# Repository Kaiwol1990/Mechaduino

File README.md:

Derivation of the original Mechaduino code from jcchurch13.

# Firmware
### Changes:

- added an enable pin (pin 2, only 3.3 V compatible)
- Menu entry for generating a step response
- Menu entry for generating a dirac delta function
- deleted all modes other than position 
- changed all float to integer operations
- added some filtering to the effort and D-Term
- Changed the frequency of the PID loop to 5 kHz
- Encoder readings are placed in its own ISR that runs with 10 kHz (oversampling)
- maximal step frequency = 40 kHz
- changed the PWM resolution from 8 bit to 9 bit
- PID auto tuning
- The lookup table is now in its own file (lookup_table.cpp)
- The Parameters are now in Configuration.cpp
- Added Language file for easy translation
- added an invert direction setting
- simple error register to save if an error occurred
- LED shows errors by different blinking patterns
- downhill simplex algorithm to fine tune the pid settings

### LED blink pattern:
If an error occures the led will switch from constant on to different patterns. These patterns are separated from each other by a longer pause. After this pause one pattern will be shown and then after the pause the next pattern will be shown.

|Pattern| Error|
|-------|------|
|Fast blinking | Timing error. This can occur if the mechaduino receives too much steps. Consider lowering your microsteps or limit the maximal speed|
|Long on | maximal error was reached|
|Long on, one flash | the maximal current was reached|
|Long on, two flashs | the lookup table shows some errors|

### List of commands
To get an list of the possible commands send help over the serial monitor

|Command|Description|Arguments|
|-------|-----------|---------|
|help | prints this menu |
|calibrate | starts the calibration routine | -check -smooth |
|diagnose | read Encoder Diagnostics | |
|state | shows and sets the motor state | -on, -off |
|stream | streams servo parameters | -f {int}, -on, -off |
|parameter | Get or set parameter | -set {-parameter} {value}, -get |
|error | get or reset the error register | -reset |
|dirac | generates a Delta-Distribution | -f {int} |
|response | generates a step response | -f {int}, -s {int} |
|error | get or reset the error register | -reset |
|autotune | PID auto tune | -c {byte}, -d |
|downhill | Downhhill simplex algorithm | -f {int}, -v {int}, -o |
|testmove | Starts a testmove for the servo | -f {int}, -v {int}, -o |
|interrupt | Starts or stops the ISR | -TC5 {bool}, -TC4 {bool} |

# Windows GUI

- Live view/stream motor parameter (angle, error, effort, ...)
- generate and analyze different test moves with different sampling rates (step response, dirac delta function, ...)
- change parameters without the need of serial commands
- generate a configuration file 
- Log streamed motor parameter as txt or csv file

# License
All Mechaduino related materials are released under the Creative Commons Attribution Share-Alike 4.0 License
https://creativecommons.org/licenses/by-sa/4.0/

Much of the work is based on Mechaduino project:
https://github.com/jcchurch13/Mechaduino-Firmware

# Support
If you want to support me for further improvements and things like that, you can send me a small kickback with PayPal

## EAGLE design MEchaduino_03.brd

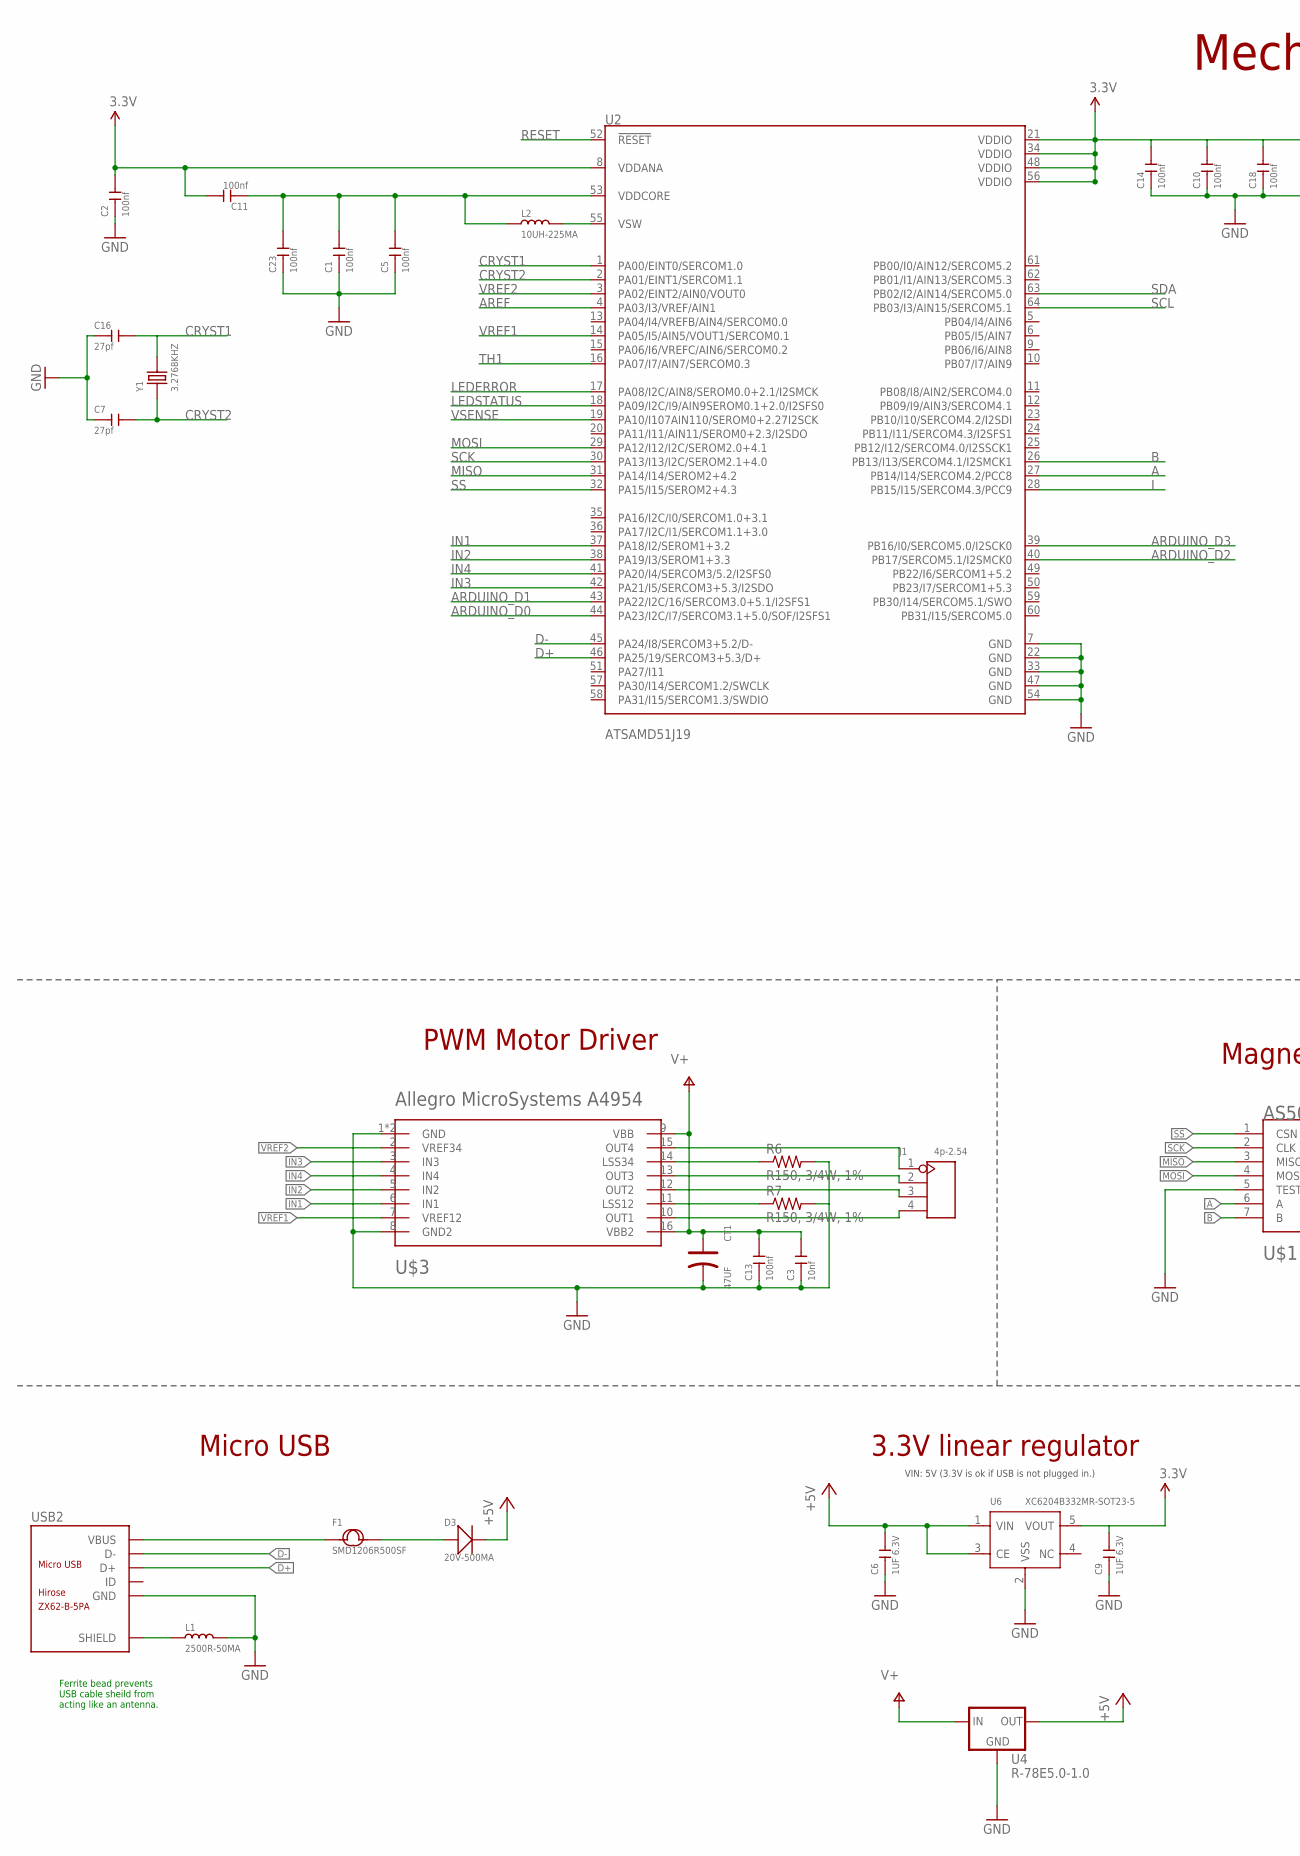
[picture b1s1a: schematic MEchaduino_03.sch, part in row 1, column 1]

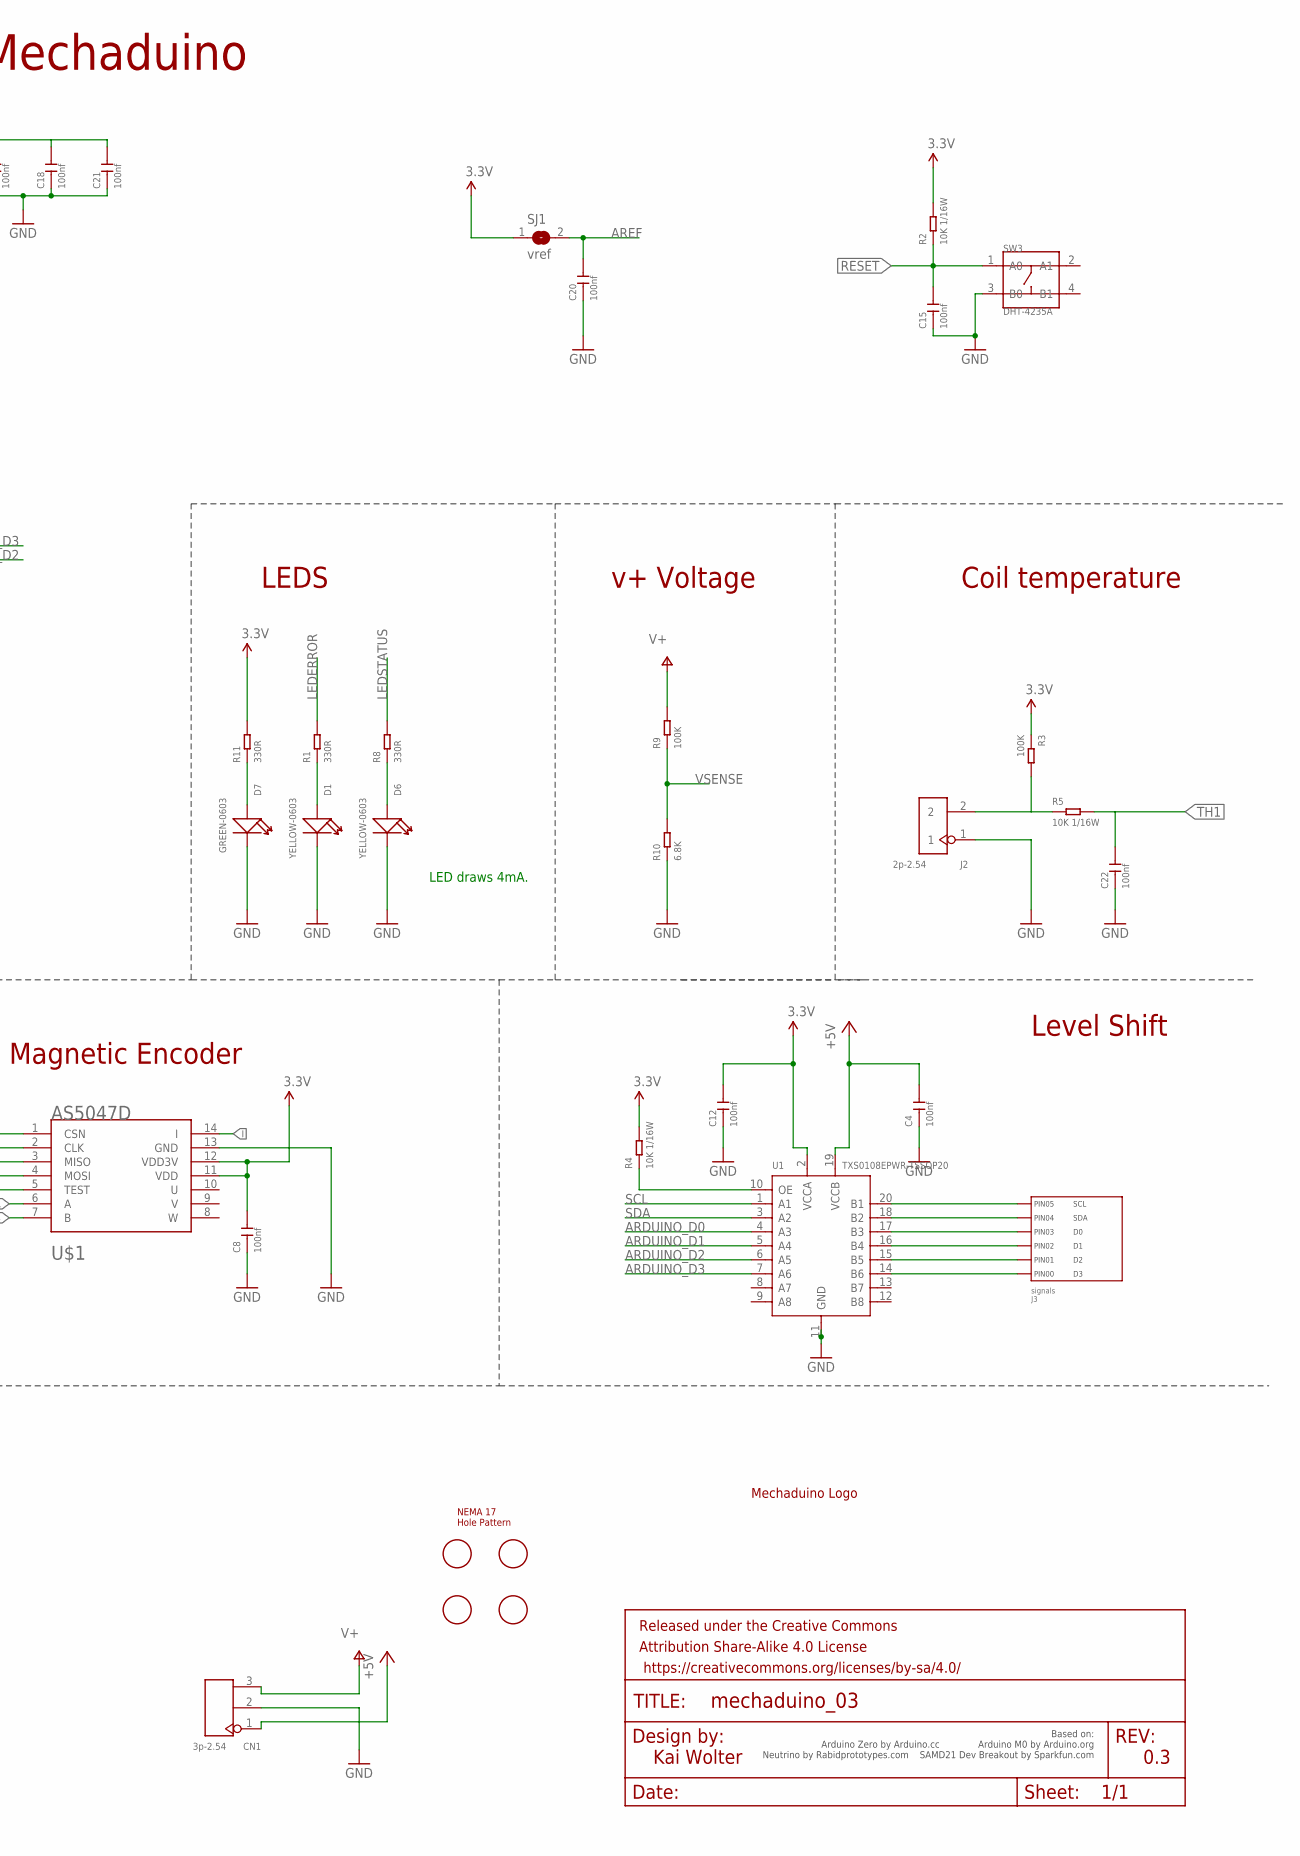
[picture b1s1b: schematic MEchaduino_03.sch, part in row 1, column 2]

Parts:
C1, C2, C4, C5, C8, C10, C11, C12, C14, C15, C18, C20, C21, C22, C23: 100nf; C0402
C3: 10nf; C0603
C6, C9: 1UF 6.3V; C0402
C7, C16: 27pf; C0402
C13: 100nf; C0603
CN1: 3p-2.54; H3-2.54
CT1: 47UF; ELECTRO-SMD-C-6MM
D1, D6: YELLOW-0603; LED-0603
D3: 20V-500MA; SOD-123
D7: GREEN-0603; LED-0603
F1: SMD1206R500SF; F1206
FRAME1: FRAME-LEDGER; CREATIVE_COMMONS
J1: 4p-2.54; H4-2.54
J2: 2p-2.54; H2-2.54
J3: signals; PTH_2.54MM_01X06
L1: 2500R-50MA; L0603
L2: 10UH-225MA; L0806
R1, R8, R11: 330R; R0402
R2, R4, R5: 10K 1/16W; R0402
R3, R9: 100K; R0402
R6, R7: R150, 3/4W, 1%; R1206; MPN KRL1632E-M-R150-F-T5
R10: 6.8K; R0603
SJ1: vref; SJ
SW3: DHT-4235A; SW4-SMD-4.2X3.2X2.5MM
U1: TXS0108EPWR-TSSOP20; TSSOP20-0.65-6.5X4.4MM
U2: ATSAMD51J19; TQFP64; MPN ATSAMD51J19A-AU
U4: R-78E5.0-1.0; DC-DC_CONVERTER_78XX
U6: XC6204B332MR-SOT23-5; SOT-23-5
U$1: AS5047D; TSSOP14; MPN AS5047D-ATSM
U$2: NEMA17_HOLE_PATTERNNEW; NEMA17_HOLE_PATTERN_2
U$3: Allegro MicroSystems A4954; TSSOP16_THERM; MPN A4953ELJTR-T
U$4: MECHADUINO_LOGO
USB2: ZX62-B-5PA; MICRO-USB5+6P-SMD-0.65-AB
Y1: 3.2768KHZ; X2-SMD-L2.0X1.2X0.55MM

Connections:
3.3V: C2.2, C8.2, C9.2, C10.2, C11.2, C12.2, C14.2, C18.2, C21.2, R2.2, R3.1, R4.2, R11.2, SJ1.1, U1.2 (VCCA), U2.8 (VDDANA), U2.21 (VDDIO), U2.34 (VDDIO), U2.48 (VDDIO), U2.56 (VDDIO), U6.5 (VOUT), U$1.11 (VDD), U$1.12 (VDD3V)
+5V: C4.2, C6.2, CN1.1, D3.-, U1.19 (VCCB), U4.VOUT (OUT), U6.1 (VIN), U6.3 (CE)
A: U2.27 (PB14/I14/SERCOM4.2/PCC8), U$1.6 (A)
ARDUINO_D0: U1.4 (A3), U2.44 (PA23/I2C/I7/SERCOM3.1+5.0/SOF/I2SFS1)
ARDUINO_D1: U1.5 (A4), U2.43 (PA22/I2C/16/SERCOM3.0+5.1/I2SFS1)
ARDUINO_D2: U1.6 (A5), U2.40 (PB17/SERCOM5.1/I2SMCK0)
ARDUINO_D3: U1.7 (A6), U2.39 (PB16/I0/SERCOM5.0/I2SCK0)
AREF: C20.2, SJ1.2, U2.4 (PA03/I3/VREF/AIN1)
B: U2.26 (PB13/I13/SERCOM4.1/I2SMCK1), U$1.7 (B)
CRYST1: C16.2, U2.1 (PA00/EINT0/SERCOM1.0), Y1.2
CRYST2: C7.2, U2.2 (PA01/EINT1/SERCOM1.1), Y1.1
D+: U2.46 (PA25/19/SERCOM3+5.3/D+), USB2.3 (D+)
D-: U2.45 (PA24/I8/SERCOM3+5.2/D-), USB2.2 (D-)
GND: C1.1, C2.1, C3.1, C4.1, C5.1, C6.1, C7.1, C8.1, C9.1, C10.1, C12.1, C13.1, C14.1, C15.1, C16.1, C18.1, C20.1, C21.1, C22.1, C23.1, CN1.2, CT1.-, D1.-, D6.-, D7.-, J2.1, L1.2, R6.2, R7.2, R10.1, SW3.3 (B0), U1.11 (GND), U2.7 (GND), U2.22 (GND), U2.33 (GND), U2.47 (GND), U2.54 (GND), U4.GND, U6.2 (VSS), U$1.5 (TEST), U$1.13 (GND), U$3.1 (GND), U$3.8 (GND2), U$3.P$1 (GND), USB2.5 (GND)
I: U2.28 (PB15/I15/SERCOM4.3/PCC9), U$1.14 (I)
IN1: U2.37 (PA18/I2/SEROM1+3.2), U$3.6 (IN1)
IN2: U2.38 (PA19/I3/SEROM1+3.3), U$3.5 (IN2)
IN3: U2.42 (PA21/I5/SERCOM3+5.3/I2SDO), U$3.3 (IN3)
IN4: U2.41 (PA20/I4/SERCOM3/5.2/I2SFS0), U$3.4 (IN4)
I_SENSE_COIL_A: R7.1, U$3.11 (LSS12)
I_SENSE_COIL_B: R6.1, U$3.14 (LSS34)
LEDERROR: R1.2, U2.17 (PA08/I2C/AIN8/SEROM0.0+2.1/I2SMCK)
LEDSTATUS: R8.2, U2.18 (PA09/I2C/I9/AIN9SEROM0.1+2.0/I2SFS0)
MISO: U2.31 (PA14/I14/SEROM2+4.2), U$1.3 (MISO)
MOSI: U2.29 (PA12/I12/I2C/SEROM2.0+4.1), U$1.4 (MOSI)
unnamed: D6.+, R8.1
unnamed: J3.P$4 (PIN3), U1.17 (B3)
unnamed: D1.+, R1.1
unnamed: J3.P$3 (PIN2), U1.16 (B4)
unnamed: J3.P$2 (PIN1), U1.15 (B5)
unnamed: R4.1, U1.10 (OE)
unnamed: J3.P$1 (PIN0), U1.14 (B6)
unnamed: C1.2, C5.2, C11.1, C23.2, L2.1, U2.53 (VDDCORE)
unnamed: J3.P$6 (PIN5), U1.20 (B1)
unnamed: L2.2, U2.55 (VSW)
unnamed: D7.+, R11.1
unnamed: D3.+, F1.2
unnamed: J1.1, U$3.15 (OUT4)
unnamed: J1.4, U$3.10 (OUT1)
unnamed: J1.3, U$3.12 (OUT2)
unnamed: J1.2, U$3.13 (OUT3)
unnamed: J3.P$5 (PIN4), U1.18 (B2)
unnamed: J2.2, R3.2, R5.1
RESET: C15.2, R2.1, SW3.1 (A0), U2.52 (!RESET!)
SCK: U2.30 (PA13/I13/I2C/SEROM2.1+4.0), U$1.2 (CLK)
SCL: U1.1 (A1), U2.64 (PB03/I3/AIN15/SERCOM5.1)
SDA: U1.3 (A2), U2.63 (PB02/I2/AIN14/SERCOM5.0)
SHIELD: L1.1, USB2.P1 (SHIELD), USB2.P2 (SHIELD), USB2.P3 (SHIELD), USB2.P4 (SHIELD), USB2.P5 (SHIELD), USB2.P6 (SHIELD)
SS: U2.32 (PA15/I15/SEROM2+4.3), U$1.1 (CSN)
TH1: C22.2, R5.2, U2.16 (PA07/I7/AIN7/SERCOM0.3)
V+: C3.2, C13.2, CN1.3, CT1.+, R9.2, U4.VIN (IN), U$3.9 (VBB), U$3.16 (VBB2)
VBUS: F1.1, USB2.1 (VBUS)
VREF1: U2.14 (PA05/I5/AIN5/VOUT1/SERCOM0.1), U$3.7 (VREF12)
VREF2: U2.3 (PA02/EINT2/AIN0/VOUT0), U$3.2 (VREF34)
VSENSE: R9.1, R10.2, U2.19 (PA10/I107AIN110/SEROM0+2.27I2SCK)

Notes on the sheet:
LED draws 4mA.
Ferrite bead prevents USB cable sheild from acting like an antenna.
3.3V linear regulator
Magnetic Encoder
PWM Motor Driver
VIN: 5V (3.3V is ok if USB is not plugged in.)
Micro USB
Kai Wolter
Based on: Arduino Zero by Arduino.cc Arduino M0 by Arduino.org Neutrino by Rabidprototypes.com SAMD21 Dev Breakout by Sparkfun.com
0.3
Mechaduino
Level Shift
Coil temperature
v+ Voltage
LEDS

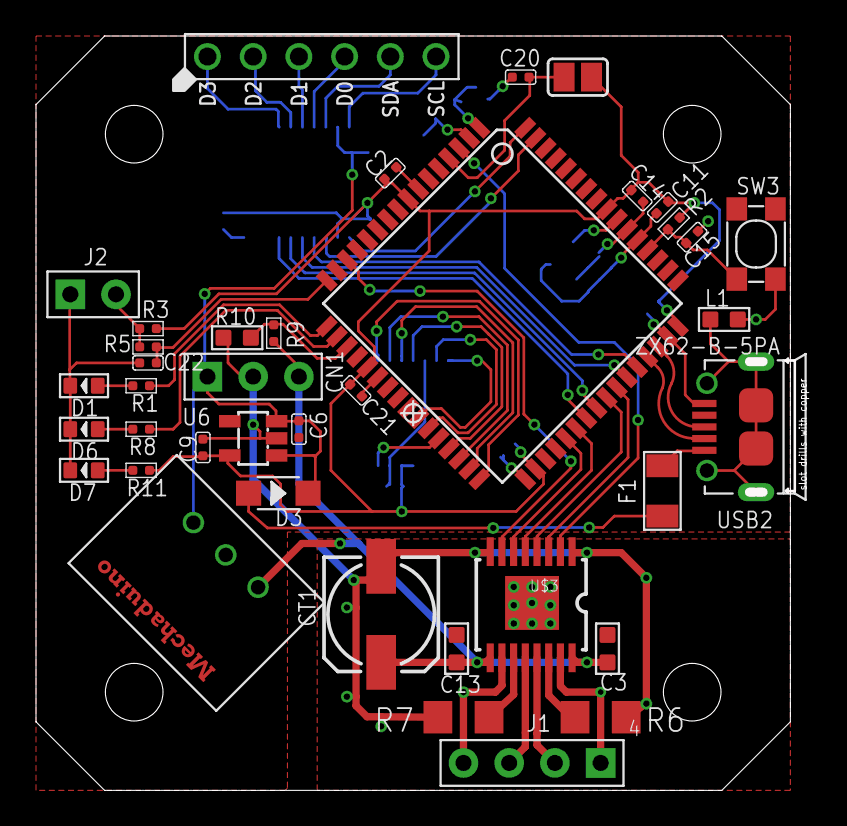
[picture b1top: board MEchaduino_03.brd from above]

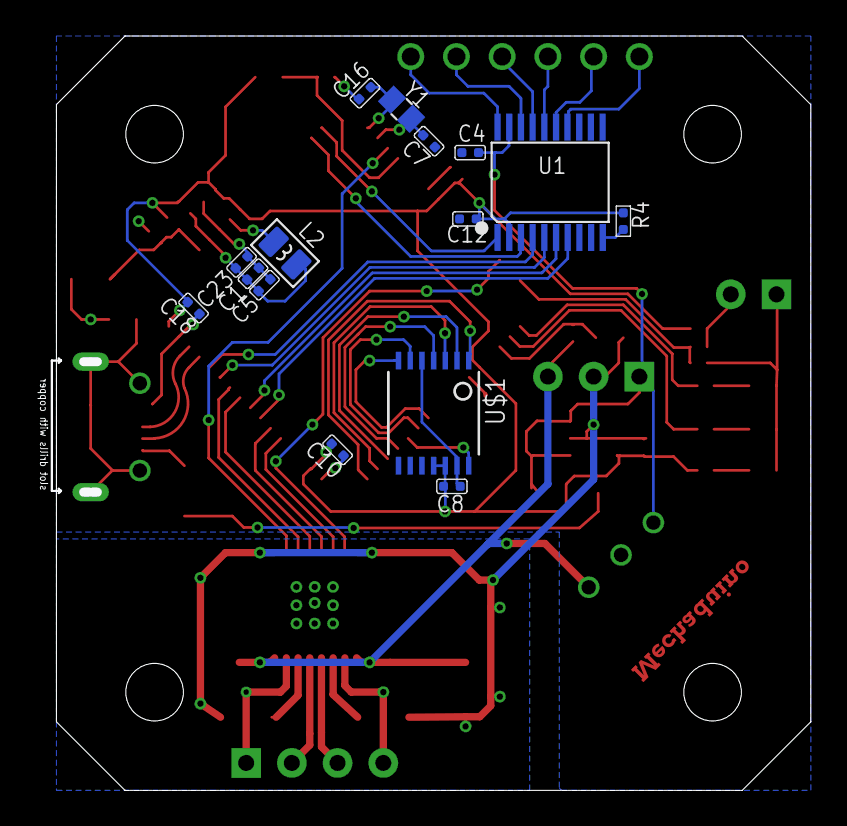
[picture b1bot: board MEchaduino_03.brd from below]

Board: 2 copper layers, 41.9 x 41.9 mm, 57 parts (15 on the bottom side), 55 nets.

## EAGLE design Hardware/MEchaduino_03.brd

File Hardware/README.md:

Derivation of the original Mechaduino code from jcchurch13.

# Firmware
### Changes:

- added an enable pin (pin 2, only 3.3 V compatible)
- Menu entry for generating a step response
- Menu entry for generating a dirac delta function
- deleted all modes other than position 
- changed all float to integer operations
- added some filtering to the effort and D-Term
- Changed the frequency of the PID loop to 5 kHz
- Encoder readings are placed in its own ISR that runs with 10 kHz (oversampling)
- maximal step frequency = 40 kHz
- changed the PWM resolution from 8 bit to 9 bit
- PID auto tuning
- The lookup table is now in its own file (lookup_table.cpp)
- The Parameters are now in Configuration.cpp
- Added Language file for easy translation
- added an invert direction setting
- simple error register to save if an error occurred
- LED shows errors by different blinking patterns
- downhill simplex algorithm to fine tune the pid settings

### LED blink pattern:
If an error occures the led will switch from constant on to different patterns. These patterns are separated from each other by a longer pause. After this pause one pattern will be shown and then after the pause the next pattern will be shown.

|Pattern| Error|
|-------|------|
|Fast blinking | Timing error. This can occur if the mechaduino receives too much steps. Consider lowering your microsteps or limit the maximal speed|
|Long on | maximal error was reached|
|Long on, one flash | the maximal current was reached|
|Long on, two flashs | the lookup table shows some errors|

### List of commands
To get an list of the possible commands send help over the serial monitor

|Command|Description|Arguments|
|-------|-----------|---------|
|help | prints this menu |
|calibrate | starts the calibration routine | |
|diagnose | read Encoder Diagnostics | |
|state | shows and sets the motor state | -on, -off |
|stream | streams servo parameters | -f {int}, -on, -off |
|parameter | Get or set parameter | -set {-parameter} {value}, -get |
|error | get or reset the error register | -reset |
|dirac | generates a Delta-Distribution | -f {int} |
|response | generates a step response | -f {int}, -s {int} |
|error | get or reset the error register | -reset |
|autotune | PID auto tune | -c {byte}, -d |
|downhill | Downhhill simplex algorithm | -f {int}, -v {int}, -o |
|testmove | Starts a testmove for the servo | -f {int}, -v {int}, -o |
|interrupt | Starts or stops the ISR | -TC5 {bool}, -TC4 {bool} |

#### Examples
|Command|Description|
|-------|-----------|
|parameter -set -Kp 1.095 | Sets the proportional gain of the servo to 1.095 |
|testmove -f 2500 -v 60 | Starts a test move with the velocity of 60 mm/s and a sampling rate of 2500 Hz |
|testmove -v 60 -o | Starts a test move with the velocity of 60 mm/s and the default sampling rate of 5000 Hz. Outputs the sampled points to the serial monitor |

# Windows GUI

- Live view/stream motor parameter (angle, error, effort, ...)
- generate and analyze different test moves with different sampling rates (step response, dirac delta function, ...)
- change parameters without the need of serial commands
- generate a configuration file 
- Log streamed motor parameter as txt or csv file

# License
All Mechaduino related materials are released under the Creative Commons Attribution Share-Alike 4.0 License
https://creativecommons.org/licenses/by-sa/4.0/

Much of the work is based on Mechaduino project:
https://github.com/jcchurch13/Mechaduino-Firmware

# Support
If you want to support me for further improvements and things like that, you can send me a small kickback with PayPal

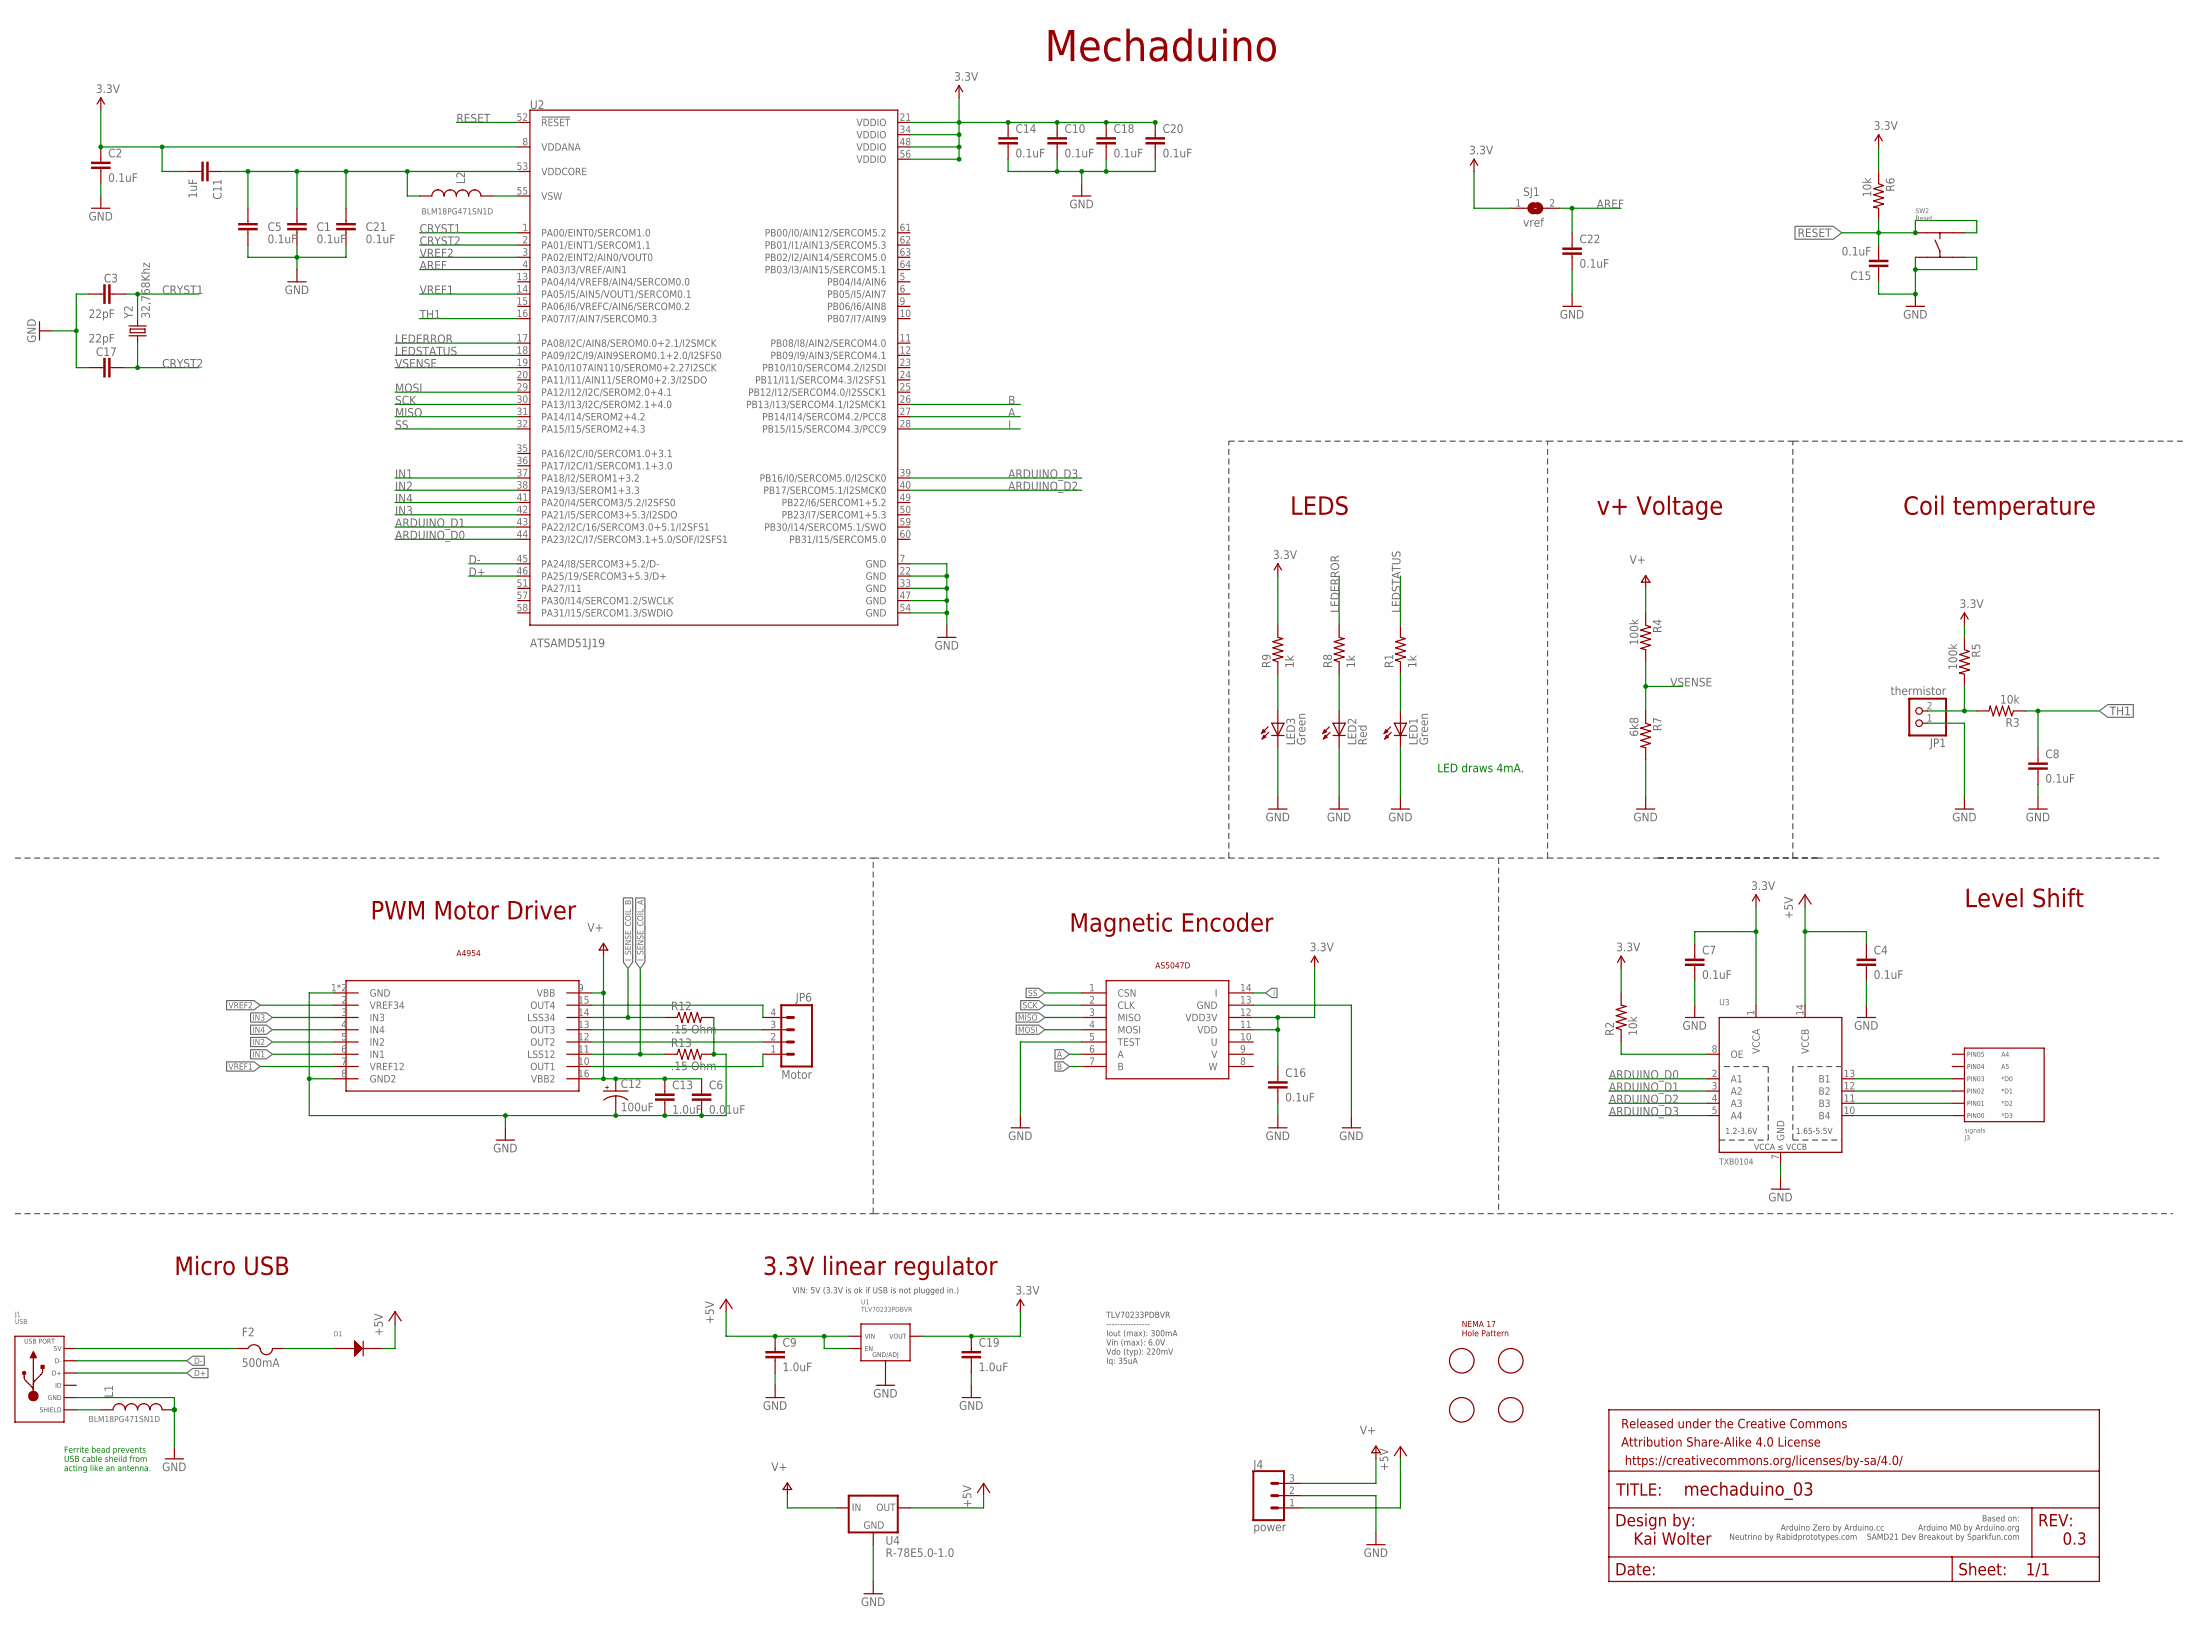
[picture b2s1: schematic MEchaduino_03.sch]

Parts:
C1, C2, C4, C5, C7, C8, C10, C14, C15, C16, C18, C20, C21, C22: 0.1uF; 0402-CAP
C3, C17: 22pF; 0603-CAP
C6: 0.01uF; 0603-CAP
C9, C19: 1.0uF; 0402-CAP
C11: 1uF; 0402-CAP
C12: 100uF; PANASONIC_D
C13: 1.0uF; 0603-CAP
D1: DIODE_SOD-123; SOD-123
F2: 500mA; R1206
FRAME1: FRAME-LEDGER; CREATIVE_COMMONS
J1: USB; MICROUSB-RIGHT
J3: signals; PTH_2.54MM_01X06
J4: power; 1X03
JP1: thermistor; 1X02
JP6: Motor; 1X04
L1, L2: BLM18PG471SN1D; 0603-TDK
LED1, LED3: Green; CHIPLED_0805
LED2: Red; CHIPLED_0805
R1, R8, R9: 1k; R0402
R2, R3, R6: 10k; R0402
R4, R5: 100k; R0402
R7: 6k8; R0402
R12, R13: .15 Ohm; R1206
SJ1: vref; SJ
SW2: Reset; TACT4.2MM
U1: TLV70233PDBVR; SOT-23-5
U2: ATSAMD51J19; TQFP64
U3: TXB0104; TSSOP14
U4: R-78E5.0-1.0; DC-DC_CONVERTER_78XX
U$1: AVAGO_DRIVERTHERM; TSSOP16_THERM
U$2: NEMA17_HOLE_PATTERNNEW; NEMA17_HOLE_PATTERN_2
U$4: AS5047D; TSSOP14
Y2: 32,768Khz; CRYSTAL-SMD-2.0X1.2

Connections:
3.3V: C2.1, C7.1, C10.1, C11.2, C14.1, C16.1, C18.1, C19.1, C20.1, R2.2, R5.1, R6.1, R9.2, SJ1.1, U1.P$5 (VOUT), U2.8 (VDDANA), U2.21 (VDDIO), U2.34 (VDDIO), U2.48 (VDDIO), U2.56 (VDDIO), U3.1 (VCCA), U$4.11 (VDD), U$4.12 (VDD3V)
+5V: C4.1, C9.1, D1.CATHODE, J4.1, U1.P$1 (VIN), U1.P$3 (EN), U3.14 (VCCB), U4.VOUT (OUT)
A: U2.27 (PB14/I14/SERCOM4.2/PCC8), U$4.6 (A)
ARDUINO_D0: U2.44 (PA23/I2C/I7/SERCOM3.1+5.0/SOF/I2SFS1), U3.2 (A1)
ARDUINO_D1: U2.43 (PA22/I2C/16/SERCOM3.0+5.1/I2SFS1), U3.3 (A2)
ARDUINO_D2: U2.40 (PB17/SERCOM5.1/I2SMCK0), U3.4 (A3)
ARDUINO_D3: U2.39 (PB16/I0/SERCOM5.0/I2SCK0), U3.5 (A4)
AREF: C22.1, SJ1.2, U2.4 (PA03/I3/VREF/AIN1)
B: U2.26 (PB13/I13/SERCOM4.1/I2SMCK1), U$4.7 (B)
CRYST1: C3.2, U2.1 (PA00/EINT0/SERCOM1.0), Y2.2
CRYST2: C17.2, U2.2 (PA01/EINT1/SERCOM1.1), Y2.1
D+: J1.3 (D+), U2.46 (PA25/19/SERCOM3+5.3/D+)
D-: J1.2 (D-), U2.45 (PA24/I8/SERCOM3+5.2/D-)
GND: C1.2, C2.2, C3.1, C4.2, C5.2, C6.2, C7.2, C8.2, C9.2, C10.2, C12.-, C13.2, C14.2, C15.1, C16.2, C17.1, C18.2, C19.2, C20.2, C21.2, C22.2, J1.5 (GND), J4.2, JP1.1, L1.2, LED1.C, LED2.C, LED3.C, R7.2, R12.2, R13.2, SW2.P$3, SW2.P$4, U1.P$2 (GND/ADJ), U2.7 (GND), U2.22 (GND), U2.33 (GND), U2.47 (GND), U2.54 (GND), U3.7 (GND), U4.GND, U$1.1 (GND), U$1.8 (GND2), U$1.P$1 (GND), U$4.5 (TEST), U$4.13 (GND)
I: U2.28 (PB15/I15/SERCOM4.3/PCC9), U$4.14 (I)
IN1: U2.37 (PA18/I2/SEROM1+3.2), U$1.6 (IN1)
IN2: U2.38 (PA19/I3/SEROM1+3.3), U$1.5 (IN2)
IN3: U2.42 (PA21/I5/SERCOM3+5.3/I2SDO), U$1.3 (IN3)
IN4: U2.41 (PA20/I4/SERCOM3/5.2/I2SFS0), U$1.4 (IN4)
I_SENSE_COIL_A: R13.1, U$1.11 (LSS12)
I_SENSE_COIL_B: R12.1, U$1.14 (LSS34)
LEDERROR: R8.2, U2.17 (PA08/I2C/AIN8/SEROM0.0+2.1/I2SMCK)
LEDSTATUS: R1.2, U2.18 (PA09/I2C/I9/AIN9SEROM0.1+2.0/I2SFS0)
MISO: U2.31 (PA14/I14/SEROM2+4.2), U$4.3 (MISO)
MOSI: U2.29 (PA12/I12/I2C/SEROM2.0+4.1), U$4.4 (MOSI)
unnamed: LED1.A, R1.1
unnamed: J3.P$4 (PIN3), U3.13 (B1)
unnamed: LED2.A, R8.1
unnamed: J3.P$3 (PIN2), U3.12 (B2)
unnamed: J3.P$2 (PIN1), U3.11 (B3)
unnamed: R2.1, U3.8 (OE)
unnamed: J3.P$1 (PIN0), U3.10 (B4)
unnamed: C1.1, C5.1, C11.1, C21.1, L2.1, U2.53 (VDDCORE)
unnamed: J1.S1 (SLD), J1.S2 (SLD), J1.S3 (SLD), J1.S4 (SLD), J1.S5 (SLD), J1.S6 (SLD), J1.S7 (SLD), J1.S8 (SLD), L1.1
unnamed: L2.2, U2.55 (VSW)
unnamed: LED3.A, R9.1
unnamed: D1.ANODE, F2.2
unnamed: JP6.4, U$1.15 (OUT4)
unnamed: JP6.1, U$1.10 (OUT1)
unnamed: JP6.2, U$1.12 (OUT2)
unnamed: JP6.3, U$1.13 (OUT3)
unnamed: JP1.2, R3.2, R5.2
unnamed: F2.1, J1.1 (5V)
RESET: C15.2, R6.2, SW2.P$1, SW2.P$2, U2.52 (!RESET!)
SCK: U2.30 (PA13/I13/I2C/SEROM2.1+4.0), U$4.2 (CLK)
SS: U2.32 (PA15/I15/SEROM2+4.3), U$4.1 (CSN)
TH1: C8.1, R3.1, U2.16 (PA07/I7/AIN7/SERCOM0.3)
V+: C6.1, C12.+, C13.1, J4.3, R4.1, U4.VIN (IN), U$1.9 (VBB), U$1.16 (VBB2)
VREF1: U2.14 (PA05/I5/AIN5/VOUT1/SERCOM0.1), U$1.7 (VREF12)
VREF2: U2.3 (PA02/EINT2/AIN0/VOUT0), U$1.2 (VREF34)
VSENSE: R4.2, R7.1, U2.19 (PA10/I107AIN110/SEROM0+2.27I2SCK)

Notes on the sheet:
LED draws 4mA.
Ferrite bead prevents USB cable sheild from acting like an antenna.
3.3V linear regulator
Magnetic Encoder
PWM Motor Driver
VIN: 5V (3.3V is ok if USB is not plugged in.)
TLV70233PDBVR ---------------- Iout (max): 300mA Vin (max): 6.0V Vdo (typ): 220mV Iq: 35uA
A4954
Micro USB
Kai Wolter
Based on: Arduino Zero by Arduino.cc Arduino M0 by Arduino.org Neutrino by Rabidprototypes.com SAMD21 Dev Breakout by Sparkfun.com
0.3
Mechaduino
Level Shift
Coil temperature
v+ Voltage
LEDS

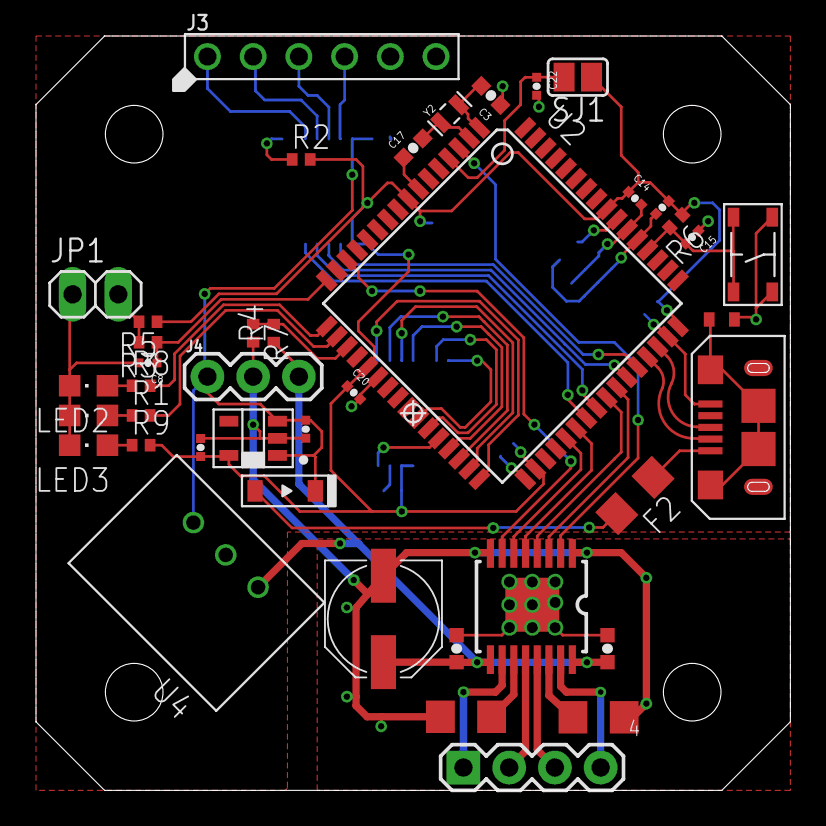
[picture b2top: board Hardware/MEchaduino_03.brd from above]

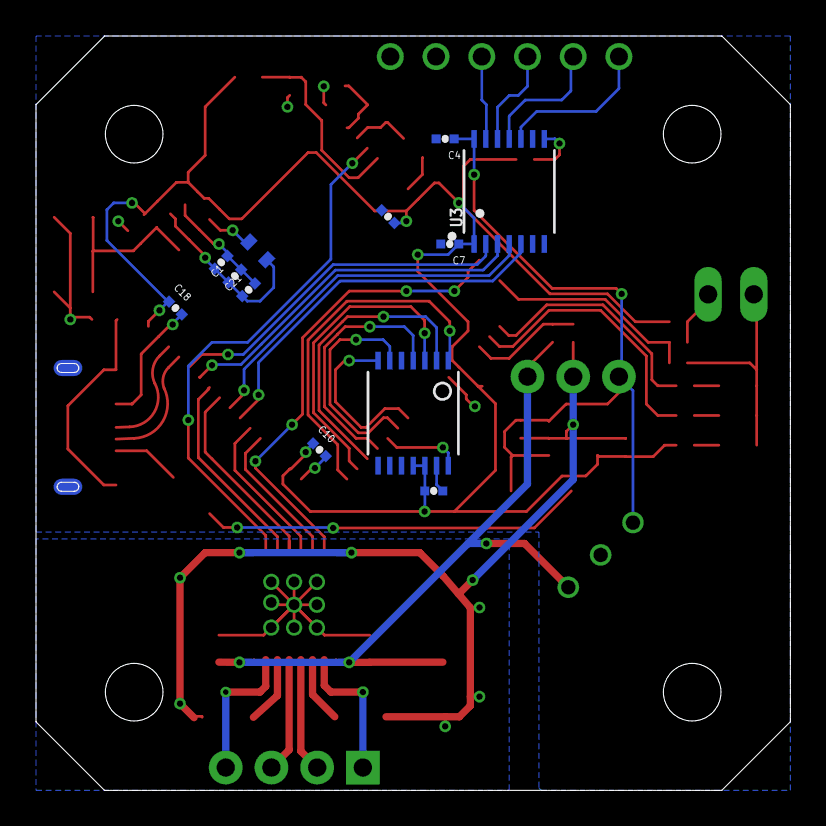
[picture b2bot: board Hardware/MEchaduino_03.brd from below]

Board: 2 copper layers, 41.9 x 41.9 mm, 56 parts (12 on the bottom side), 51 nets.

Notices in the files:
parts and their libraries:
SparkFun-Connectors: Licensing: Creative Commons ShareAlike 4.0 International - https://creativecommons.org/licenses/by-sa/4.0
